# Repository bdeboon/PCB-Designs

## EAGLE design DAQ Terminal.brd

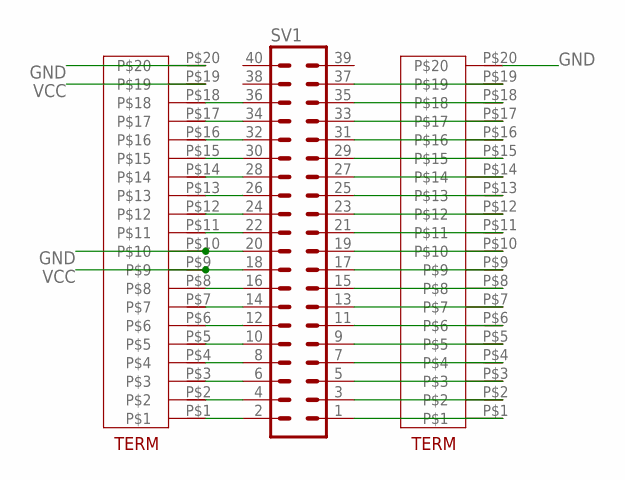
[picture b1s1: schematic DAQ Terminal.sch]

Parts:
SV1: MA20-2
U$1, U$2: 20TERM

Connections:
GND: SV1.20, U$1.P$20, U$2.P$10, U$2.P$20
unnamed: SV1.2, U$2.P$1
unnamed: SV1.4, U$2.P$2
unnamed: SV1.6, U$2.P$3
unnamed: SV1.8, U$2.P$4
unnamed: SV1.10, U$2.P$5
unnamed: SV1.12, U$2.P$6
unnamed: SV1.14, U$2.P$7
unnamed: SV1.16, U$2.P$8
unnamed: SV1.22, U$2.P$11
unnamed: SV1.24, U$2.P$12
unnamed: SV1.26, U$2.P$13
unnamed: SV1.28, U$2.P$14
unnamed: SV1.30, U$2.P$15
unnamed: SV1.32, U$2.P$16
unnamed: SV1.34, U$2.P$17
unnamed: SV1.36, U$2.P$18
unnamed: SV1.1, U$1.P$1
unnamed: SV1.3, U$1.P$2
unnamed: SV1.5, U$1.P$3
unnamed: SV1.7, U$1.P$4
unnamed: SV1.9, U$1.P$5
unnamed: SV1.11, U$1.P$6
unnamed: SV1.13, U$1.P$7
unnamed: SV1.15, U$1.P$8
unnamed: SV1.17, U$1.P$9
unnamed: SV1.19, U$1.P$10
unnamed: SV1.21, U$1.P$11
unnamed: SV1.23, U$1.P$12
unnamed: SV1.25, U$1.P$13
unnamed: SV1.27, U$1.P$14
unnamed: SV1.29, U$1.P$15
unnamed: SV1.31, U$1.P$16
unnamed: SV1.33, U$1.P$17
unnamed: SV1.35, U$1.P$18
unnamed: SV1.37, U$1.P$19
VCC: SV1.18, U$2.P$9, U$2.P$19

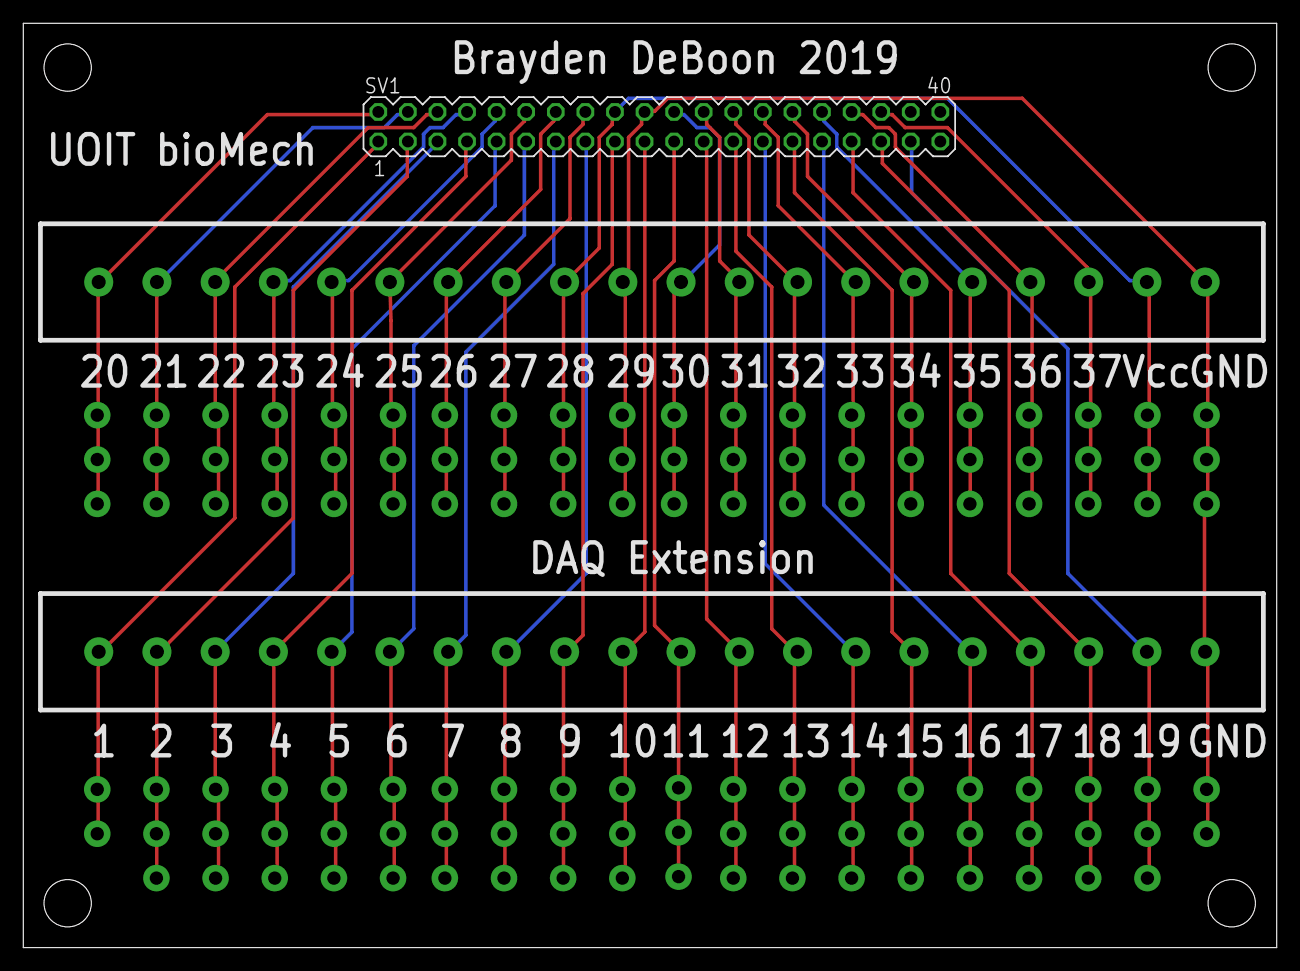
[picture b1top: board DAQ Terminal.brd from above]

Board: 2 copper layers, 107.6 x 79.4 mm, 3 parts (0 on the bottom side), 37 nets.

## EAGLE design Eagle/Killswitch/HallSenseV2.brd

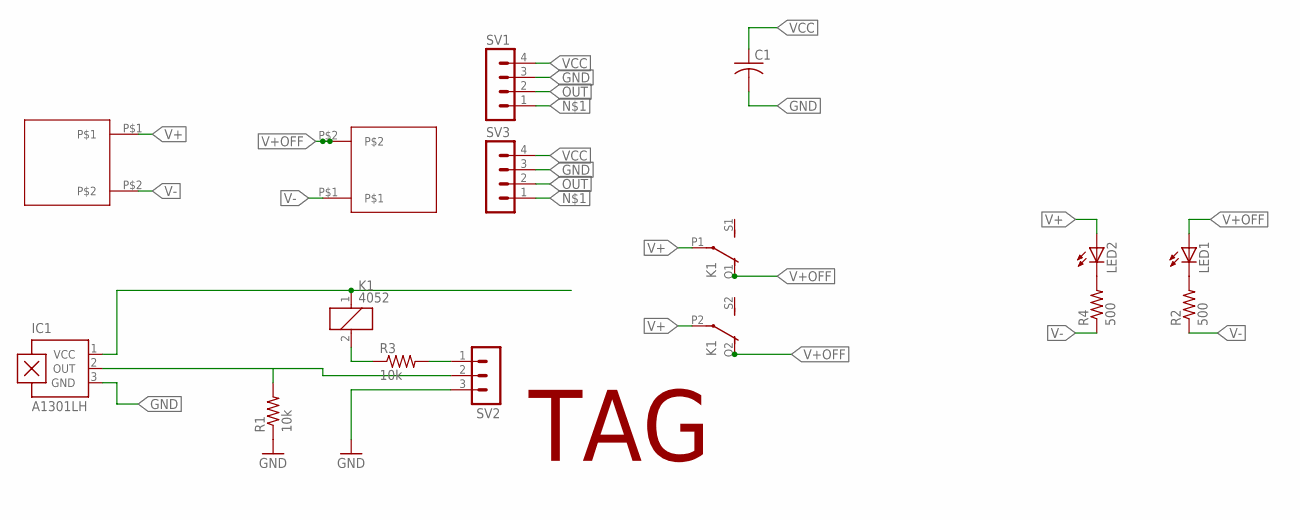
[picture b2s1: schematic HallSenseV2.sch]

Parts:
C1: C-USC0805K; C0805K
IC1: A1301LH; SOT23-W
K1: 4052; F4052
LED1, LED2: LED5MM
R1, R3: 10k; R0805
R2, R4: 500; 0207/10
SV1, SV3: MA04-1
SV2: MA03-1
U$1, U$2: TERM_POWER; TERM_BLOCK_POWER
U$3: TAG

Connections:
GND: C1.2, IC1.3 (GND), R1.1, SV1.3, SV2.3, SV3.3
unnamed: K1.2, R3.1, SV1.1, SV3.1
unnamed: LED2.K (C), R4.2
unnamed: LED1.K (C), R2.2
unnamed: R3.2, SV2.1
OUT: IC1.2 (OUT), R1.2, SV1.2, SV2.2, SV3.2
V+: K1.P1, K1.P2, LED2.A, U$1.P$1
V+OFF: K1.O1 (O), K1.O2 (O), LED1.A, U$2.P$2
V-: R2.1, R4.1, U$1.P$2, U$2.P$1
VCC: C1.1, IC1.1 (VCC), K1.1, SV1.4, SV3.4

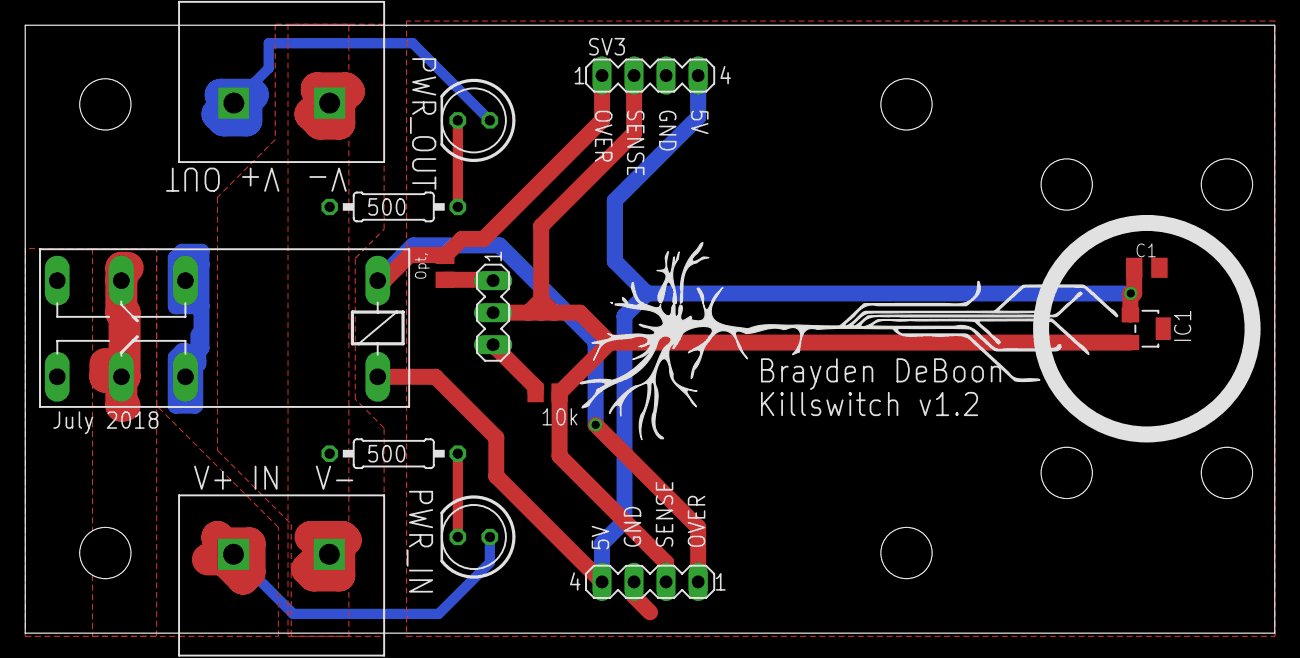
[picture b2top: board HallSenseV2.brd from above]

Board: 2 copper layers, 99.0 x 48.2 mm, 15 parts (0 on the bottom side), 10 nets.
